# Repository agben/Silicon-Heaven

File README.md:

**Silicon Heaven**
---
The afterlife for obsolete equipment and software.

For more on each entry see www.benningtons.net/index.php/category/silicon-heaven

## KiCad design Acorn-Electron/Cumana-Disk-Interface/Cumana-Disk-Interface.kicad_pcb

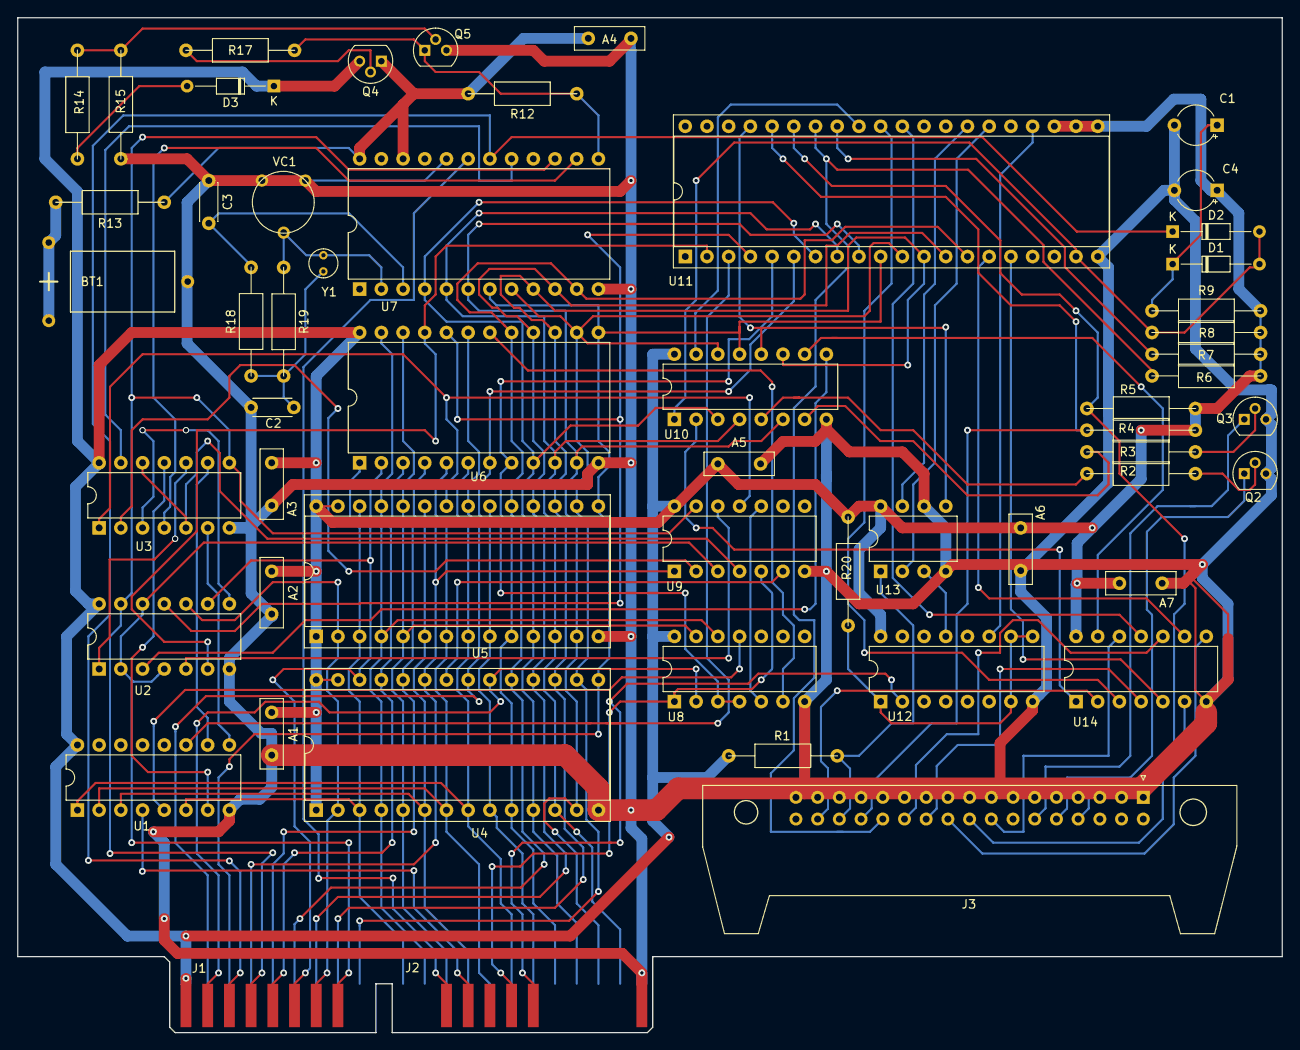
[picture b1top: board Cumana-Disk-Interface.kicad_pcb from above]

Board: 2 copper layers, 148.0 x 118.7 mm, 55 parts (0 on the bottom side), 93 nets.

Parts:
A1, A2, A3, A4, A5, A6, A7: C; C_Disc_D8.0mm_W2.5mm_P5.00mm
BT1: Battery_Cell
C1, C4: CP1; CP_Radial_Tantal_D4.5mm_P5.00mm
C2, C3: C; C_Disc_D4.3mm_W1.9mm_P5.00mm
D1, D2: Diode; D_DO-34_SOD68_P10.16mm_Horizontal
D3: D_Zener; D_DO-34_SOD68_P10.16mm_Horizontal
J1: Bottom Top; Connector_2x9_P1.27mm_Polarized_Edge
J2: CONN_12X2; Connector_2x12_P1.27mm_Polarized_Edge
J3: Conn_01x34_Female; IDC-Header_2x17_P2.54mm_Horizontal_Lock
Q2, Q3, Q5: Q_NPN_CBE; TO-92
Q4: Q_PNP_CBE; TO-92
R1, R2, R3, R4, R5, R6, R7, R8, R9, R12, R13, R14, R15, R17, R18, R19, R20: R; R_Axial_DIN0212_L12.5mm_D2.5mm_Horizontal
U1: 74LS138; DIP-16_W7.62mm
U2: 74LS00; DIP-14_W7.62mm
U3: 74LS02; DIP-14_W7.62mm
U4, U5: 27128; DIP-28_W15.24mm_Socket
U6: CDM6116; DIP-24_W15.24mm
U7: HD146818; DIP-24_W15.24mm
U8: 74LS32; DIP-14_W7.62mm
U9: 74LS04; DIP-14_W7.62mm
U10: 74LS174; DIP-16_W7.62mm
U11: M5W1793-02P; DIP-40_W15.24mm_Socket
U12: 74LS161; DIP-16_W7.62mm
U13: FDC9216B; DIP-8_W7.62mm
U14: 7406; DIP-14_W7.62mm
VC1: C_Trimmer
Y1: Crystal_Small; Crystal_D3.0mm_Vertical

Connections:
1MHz: U11.24, U12.11
4MHz: U12.13, U13.3
+5V: A1.1, A2.1, A3.1, A5.1, A6.1, A7.1, C4.1, D3.1, J1.1, J1.10, Q4.3, R1.2, R4.2, R5.2, R6.2, R7.2, R8.2, R9.2, R20.1, U1.16, U2.14, U3.14, U4.1, U4.27, U4.28, U5.1, U5.27, U5.28, U6.24, U8.14, U9.14, U10.16, U11.21, U11.22, U11.23, U12.16, U13.8, U14.14
/A0: J2.20, U4.10, U5.10, U6.8, U11.5
/A1: J2.19, U4.9, U5.9, U6.7, U11.6
/A2: J2.18, U1.1, U4.8, U5.8, U6.6
/A3: J2.17, U1.2, U4.7, U5.7, U6.5
/A4: J2.16, U1.3, U4.6, U5.6, U6.4
/A5: J2.15, U4.5, U5.5, U6.3, U8.13
/A6: J2.14, U4.4, U5.4, U6.2, U8.12
/A7: J2.13, U1.6, U4.3, U5.3, U6.1
/A8: J1.5, U4.25, U5.25, U6.23
/A9: J1.14, U4.24, U5.24, U6.22
/A10: J1.11, U4.21, U5.21, U6.19
/A11: J1.13, U4.23, U5.23, U9.1
/A12: J1.7, U2.10, U4.2, U5.2
/A13: J1.6, U2.9, U4.26, U5.26
/D0: J2.21, U4.11, U5.11, U6.9, U7.4, U10.3, U11.7
/D1: J2.23, U4.12, U5.12, U6.10, U7.5, U10.4, U11.8
/D2: J2.22, U4.13, U5.13, U6.11, U7.6, U10.6, U11.9
/D3: J1.12, U4.15, U5.15, U6.13, U7.7, U10.13, U11.10
/D4: J1.18, U4.16, U5.16, U6.14, U7.8, U10.14, U11.11
/D5: J1.17, U4.17, U5.17, U6.15, U7.9, U10.11, U11.12
/D6: J1.16, U4.18, U5.18, U6.16, U7.10, U11.13
/D7: J1.15, U4.19, U5.19, U6.17, U7.11, U11.14
Elk-16MHz: J2.7, U12.2
Elk-CPUClock: J1.8, U2.2, U2.4, U2.12, U9.3
Elk-IRQ: J2.3, U7.19
Elk-OE: J1.2, U4.20, U8.2
Elk-ROMQa: J2.6, U8.1, U9.5
Elk-ReadWrite: J1.4, U2.13, U3.8, U7.15, U9.13
Elk-Reset: D2.1, J1.3, U7.18
Elk-Select: J2.4, U1.4
FDD-Direction: J3.18, U14.6
FDD-IndexPulse: J3.8, R5.1, U11.35
FDD-MotorOn: J3.16, U14.12
FDD-Read: J3.30, R1.1, U13.1
FDD-Select0: J3.10, Q2.1
FDD-Select1: J3.12, Q3.1
FDD-Side: J3.32, U14.2
FDD-Step: J3.20, U14.8
FDD-TrackZero: J3.26, R6.1, U11.34
FDD-Write: J3.22, U14.4
FDD-WriteGate: J3.24, U14.10
FDD-WriteProtect: J3.28, R4.1, U11.36
GND: A1.2, A2.2, A3.2, A4.1, A5.2, A6.2, A7.2, BT1.2, C1.2, C2.1, C3.1, C4.2, J2.12, J2.24, J3.1, J3.3, J3.5, J3.7, J3.9, J3.11, J3.13, J3.15, J3.17, J3.19, J3.21, J3.23, J3.25, J3.27, J3.29, J3.31, J3.33, Q2.3, Q3.3, Q5.3, R15.1, U1.8, U2.7, U3.7, U4.14, U5.14, U6.12, U7.12, U7.20, U8.7, U9.7, U10.8, U11.20, U12.8, U13.4, U13.6, U14.7, VC1.2
unnamed: A4.2, Q4.1, R12.2, R13.2, U7.22, U7.24
unnamed: BT1.1, R13.1
unnamed: C1.1, D1.1, R9.1
unnamed: C2.2, R18.1, R19.2, Y1.2
unnamed: C3.2, R18.2, U7.3
unnamed: D3.2, R14.2
unnamed: Q2.2, R2.1
unnamed: Q3.2, R3.1
unnamed: Q4.2, R17.1
unnamed: Q5.1, R12.1, R17.2, U7.13
unnamed: Q5.2, R14.1, R15.2
unnamed: R2.2, U10.5
unnamed: R3.2, U10.7
unnamed: R7.1, U11.33
unnamed: R19.1, U7.2, VC1.1, Y1.1
unnamed: R20.2, U12.1, U12.7, U12.9, U12.10
unnamed: U1.5, U8.11
unnamed: U1.7, U3.11
unnamed: U1.9, U3.6
unnamed: U1.10, U3.9
unnamed: U1.11, U11.3
unnamed: U2.1, U3.10
unnamed: U2.5, U9.12
unnamed: U2.8, U3.3
unnamed: U3.1, U5.22, U9.11
unnamed: U3.2, U9.2
unnamed: U3.4, U7.14
unnamed: U3.5, U3.12, U9.4
unnamed: U3.13, U7.17
unnamed: U4.22, U9.6
unnamed: U5.20, U8.3, U8.4
unnamed: U6.18, U8.6
unnamed: U8.5, U9.10
unnamed: U10.2, U14.1
unnamed: U2.3, U10.9
unnamed: U10.10, U14.13
unnamed: U11.15, U14.9
unnamed: U11.16, U14.5
unnamed: U11.26, U13.2
unnamed: U11.27, U13.7
unnamed: U11.30, U14.11
unnamed: U11.31, U14.3
Read: U2.11, U6.20, U11.4
Ready: U10.15, U11.32
Reset: D1.2, D2.2, R8.1, U10.1, U11.19
SD-DD: U10.12, U11.37, U13.5
Write: U2.6, U6.21, U11.2

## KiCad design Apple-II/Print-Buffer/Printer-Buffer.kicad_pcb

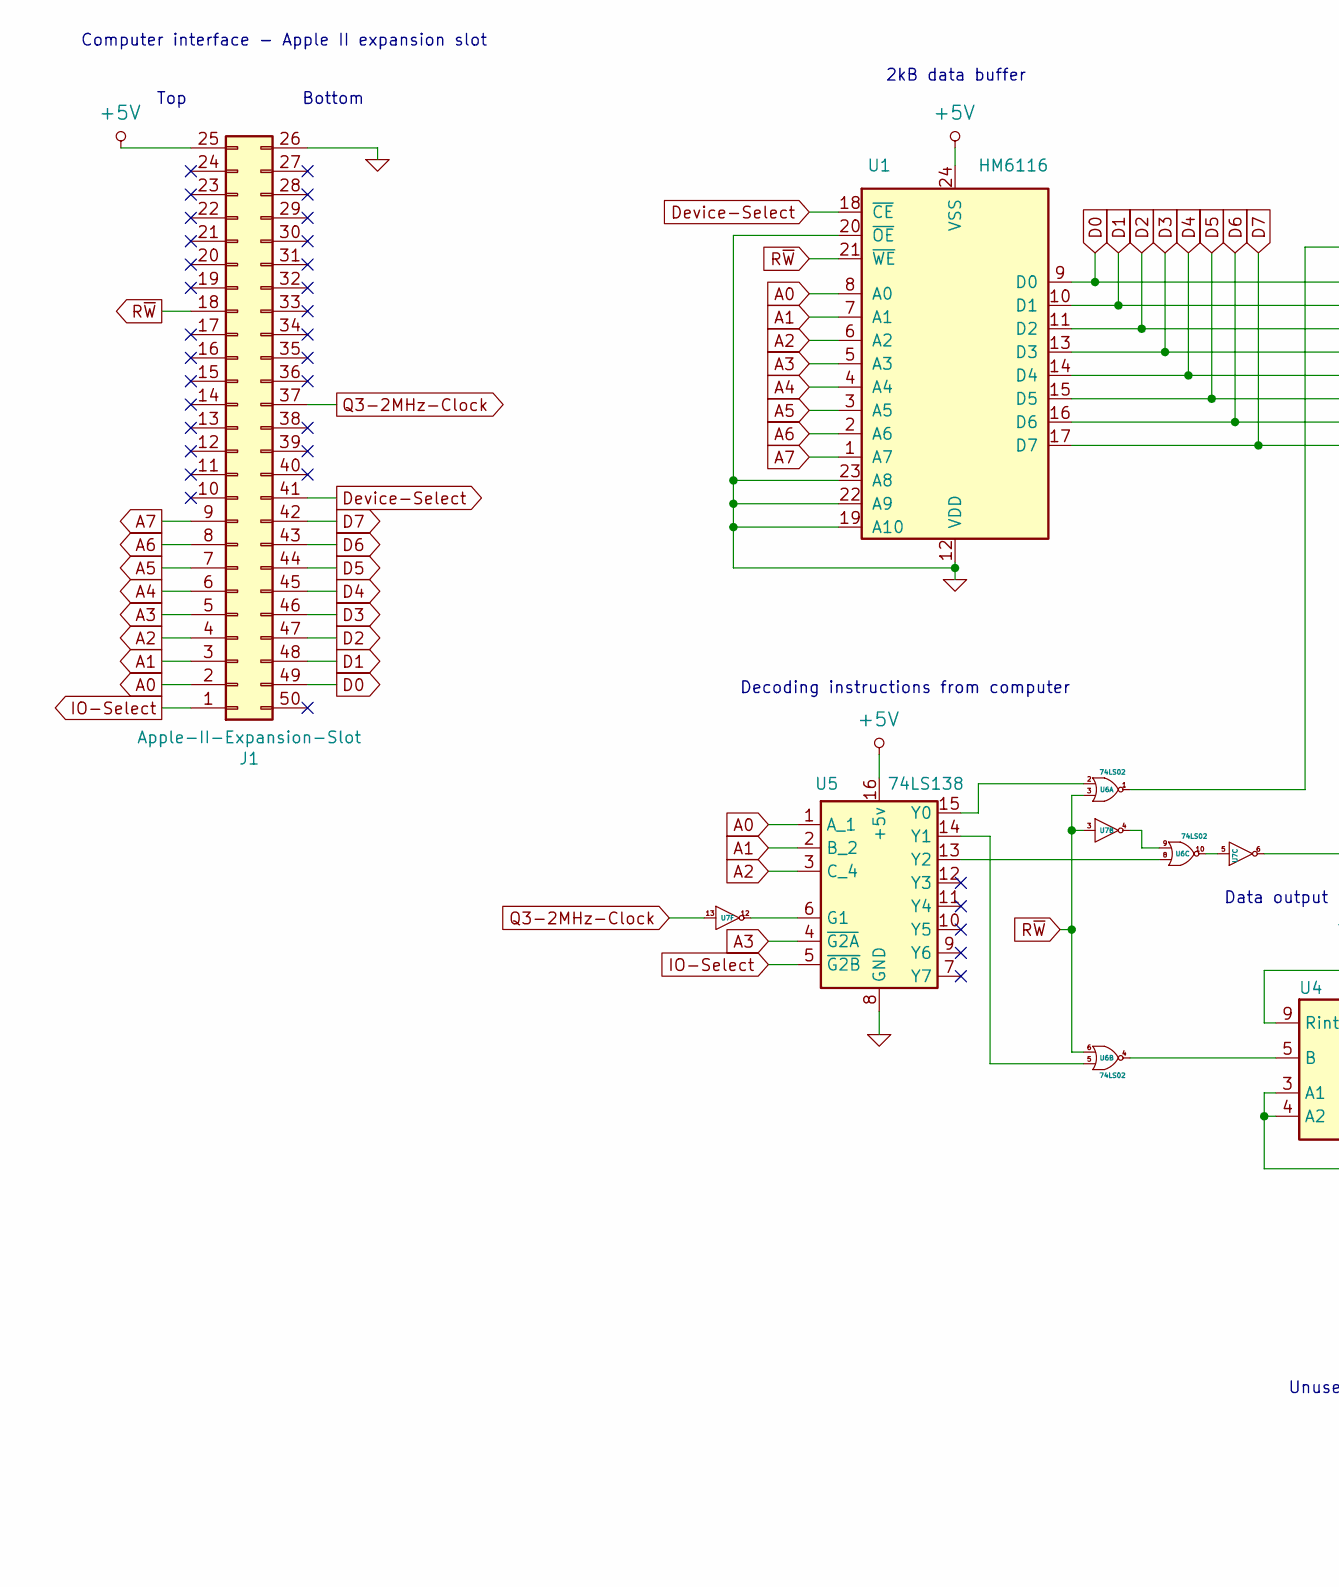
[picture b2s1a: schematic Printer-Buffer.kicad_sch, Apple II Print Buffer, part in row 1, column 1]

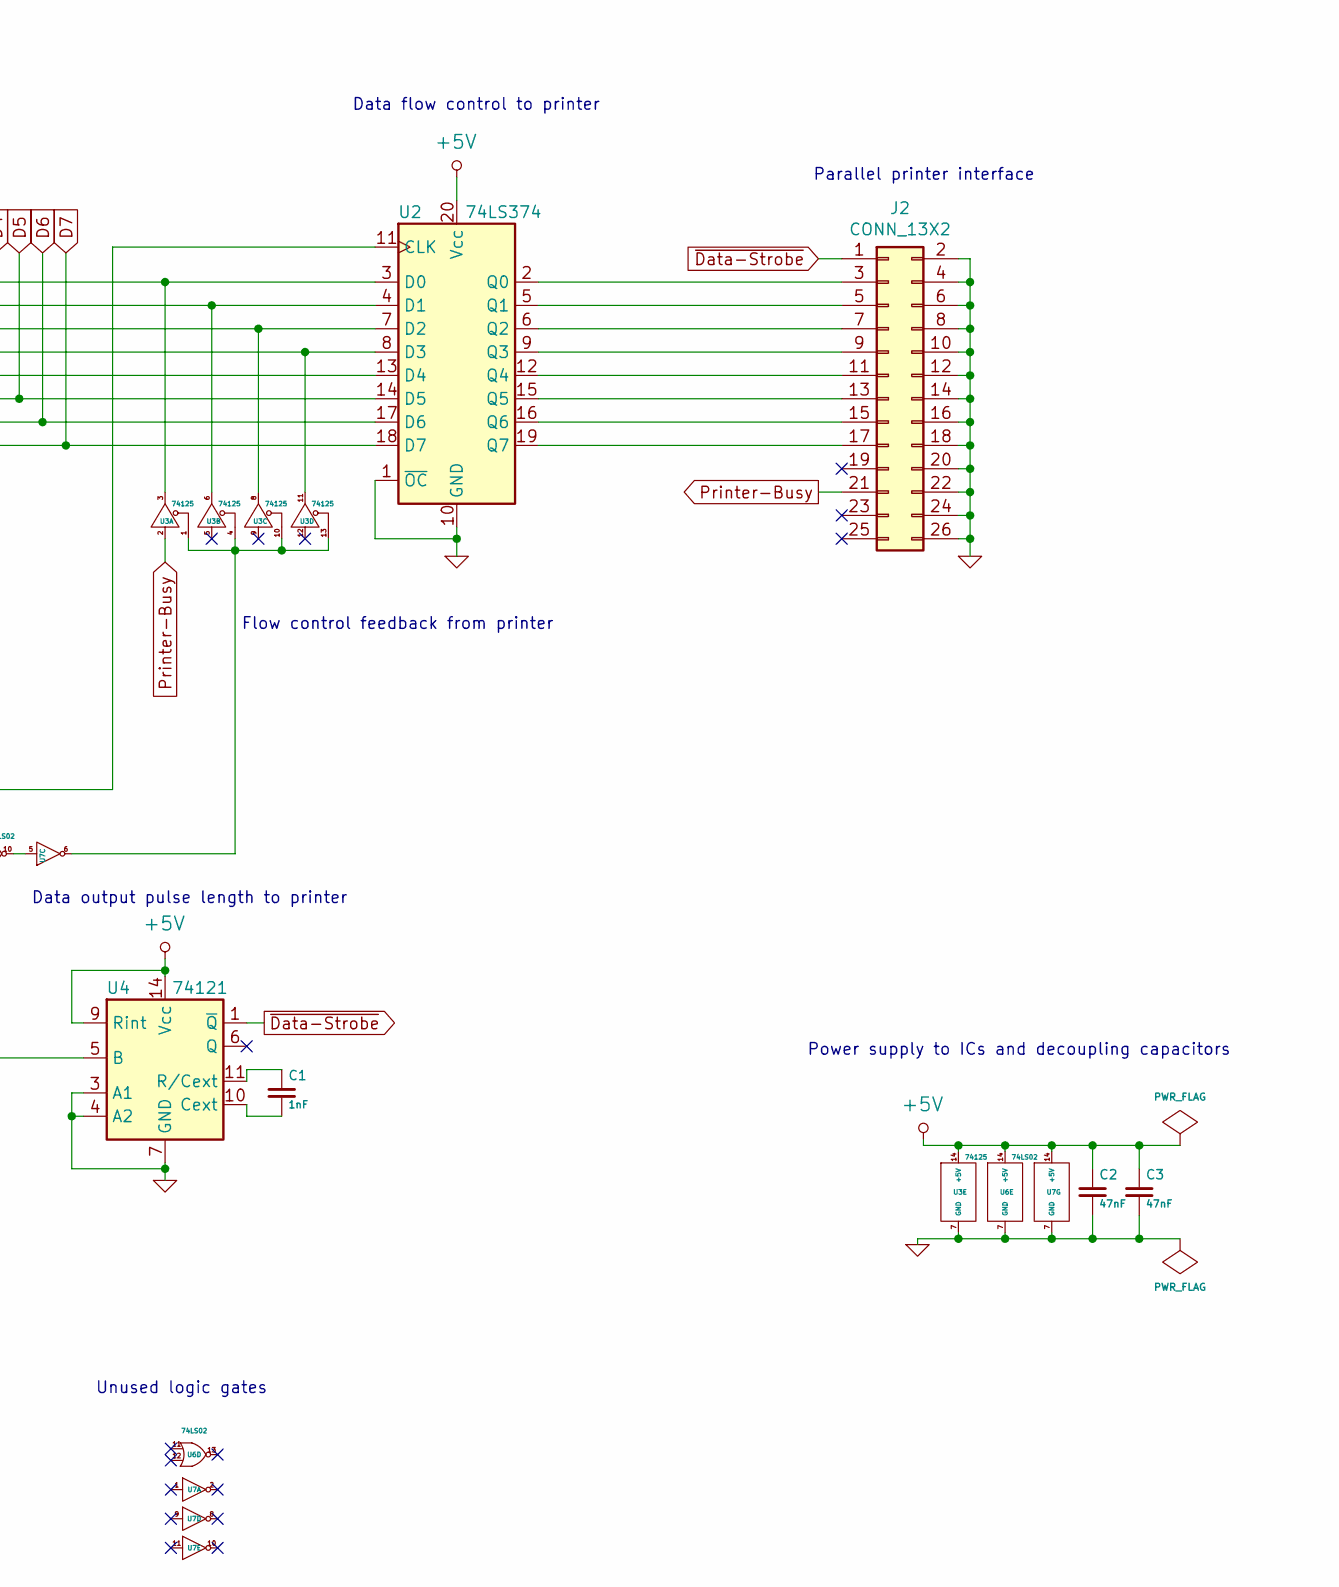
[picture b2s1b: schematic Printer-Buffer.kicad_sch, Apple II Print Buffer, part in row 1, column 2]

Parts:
C1: 1nF; C_Rect_L7.0mm_W2.0mm_P5.00mm
C2, C3: 47nF; C_Rect_L7.0mm_W2.0mm_P5.00mm
J1: Apple-II-Expansion-Slot; Connector_2x25_P1.27mm_Polarized_Edge
J2: CONN_13X2; IDC-Header_2x13_P2.54mm_Vertical_Lock
U1: HM6116; DIP-24_W15.24mm
U2: 74LS374; DIP-20_W7.62mm
U3: 74125; DIP-14_W7.62mm
U4: 74121; DIP-14_W7.62mm
U5: 74LS138; DIP-16_W7.62mm
U6: 74LS02; DIP-14_W7.62mm
U7: 7404; DIP-14_W7.62mm

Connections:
+5V: C2.1, C3.1, J1.25, U1.24 (VSS), U2.20 (Vcc), U3.14 (+5V), U4.9 (Rint), U4.14 (Vcc), U5.16 (+5v), U6.14 (+5V), U7.14 (+5V)
A0: J1.2, U1.8 (A0), U5.1 (A_1)
A1: J1.3, U1.7 (A1), U5.2 (B_2)
A2: J1.4, U1.6 (A2), U5.3 (C_4)
A3: J1.5, U1.5 (A3), U5.4 (~G2A)
A4: J1.6, U1.4 (A4)
A5: J1.7, U1.3 (A5)
A6: J1.8, U1.2 (A6)
A7: J1.9, U1.1 (A7)
D0: J1.49, U1.9 (D0), U2.3 (D0), U3.3
D1: J1.48, U1.10 (D1), U2.4 (D1), U3.6
D2: J1.47, U1.11 (D2), U2.7 (D2), U3.8
D3: J1.46, U1.13 (D3), U2.8 (D3), U3.11
D4: J1.45, U1.14 (D4), U2.13 (D4)
D5: J1.44, U1.15 (D5), U2.14 (D5)
D6: J1.43, U1.16 (D6), U2.17 (D6)
D7: J1.42, U1.17 (D7), U2.18 (D7)
Device-Select: J1.41, U1.18 (~CE)
GND: C2.2, C3.2, J1.26, J2.2, J2.4, J2.6, J2.8, J2.10, J2.12, J2.14, J2.16, J2.18, J2.20, J2.22, J2.24, J2.26, U1.12 (VDD), U1.19 (A10), U1.20 (~OE), U1.22 (A9), U1.23 (A8), U2.1 (~OC), U2.10 (GND), U3.7 (GND), U4.3 (A1), U4.4 (A2), U4.7 (GND), U5.8 (GND), U6.7 (GND), U7.7 (GND)
IO-Select: J1.1, U5.5 (~G2B)
unnamed: C1.1, U4.11 (R/Cext)
unnamed: C1.2, U4.10 (Cext)
unnamed: J2.3, U2.2 (Q0)
unnamed: J2.5, U2.5 (Q1)
unnamed: J2.7, U2.6 (Q2)
unnamed: J2.9, U2.9 (Q3)
unnamed: J2.11, U2.12 (Q4)
unnamed: J2.13, U2.15 (Q5)
unnamed: J2.15, U2.16 (Q6)
unnamed: J2.17, U2.19 (Q7)
unnamed: U2.11 (CLK), U6.1
unnamed: U3.1, U3.4, U3.10, U3.13, U7.6
unnamed: U4.5 (B), U6.4
unnamed: U5.6 (G1), U7.12
unnamed: U5.13 (Y2), U6.8
unnamed: U5.14 (Y1), U6.5
unnamed: U5.15 (Y0), U6.2
unnamed: U6.9, U7.4
unnamed: U6.10, U7.5
Printer-Busy: J2.21, U3.2
Q3-2MHz-Clock: J1.37, U7.13
R~W: J1.18, U1.21 (~WE), U6.3, U6.6, U7.3
~Data-Strobe: J2.1, U4.1 (~Q)

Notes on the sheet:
Flow control feedback from printer
Decoding instructions from computer
2kB data buffer
Top Bottom
Power supply to ICs and decoupling capacitors
Computer interface - Apple II expansion slot
Unused logic gates
Data output pulse length to printer
Parallel printer interface
Data flow control to printer

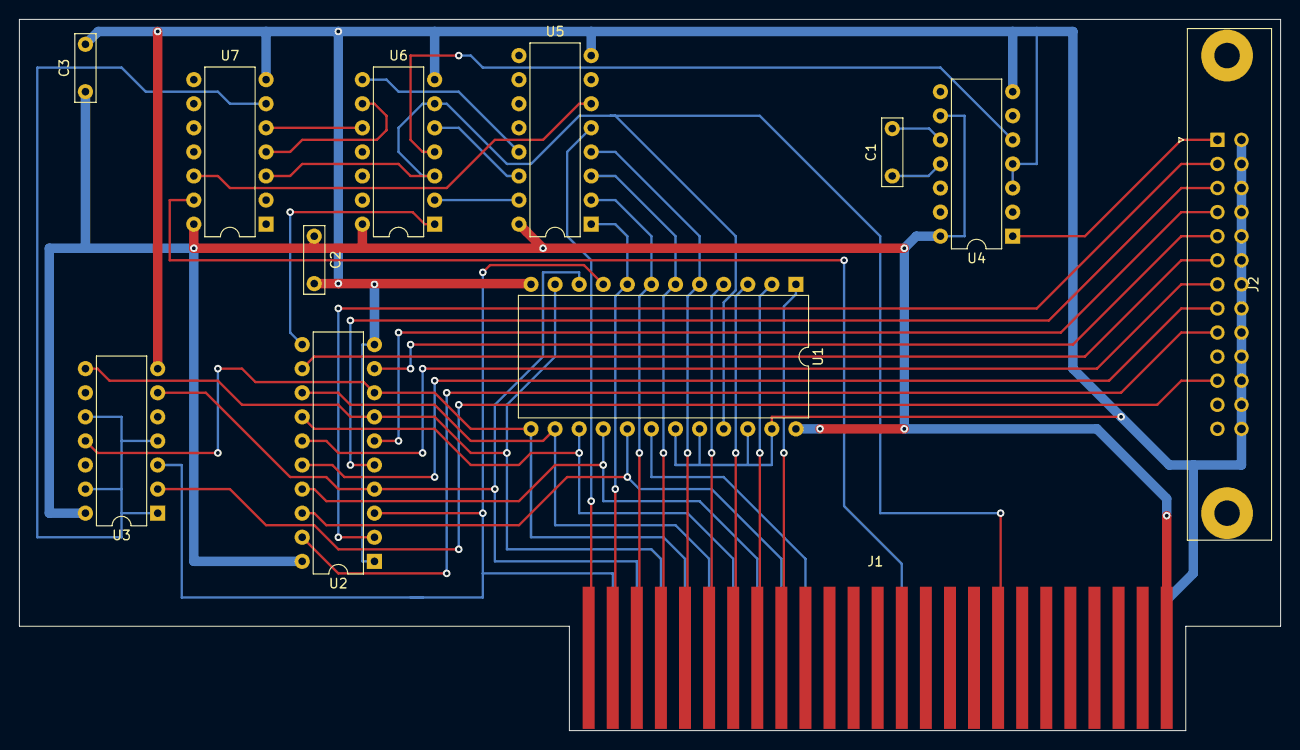
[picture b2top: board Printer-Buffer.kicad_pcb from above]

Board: 2 copper layers, 133.0 x 75.0 mm, 12 parts (0 on the bottom side), 43 nets.

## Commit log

2023-08-22 Cumana disk interface schematic
2023-08-23 Cumana disk interface schematic update and pdf
2023-08-23 Cumana disk interface schematic update
2023-08-25 Cumana disk interface - charge battery
2023-08-31 corrections and footptint selections
2023-09-05 added footprints and pcb
2023-09-13 top and bottom images of the pcb
2023-09-13 silk screen corrections
2023-09-19 bill of materials added
2023-09-20 ROM and disassembly
2023-10-18 Apple II printer buffer initial schematic
2023-10-22 netlist and footprints
2023-10-22 show values for caps and resistors
2023-10-27 PCB layout
2023-10-30 PCB tweaks and some images
2025-09-28 upgraded to KiCad 6.0
